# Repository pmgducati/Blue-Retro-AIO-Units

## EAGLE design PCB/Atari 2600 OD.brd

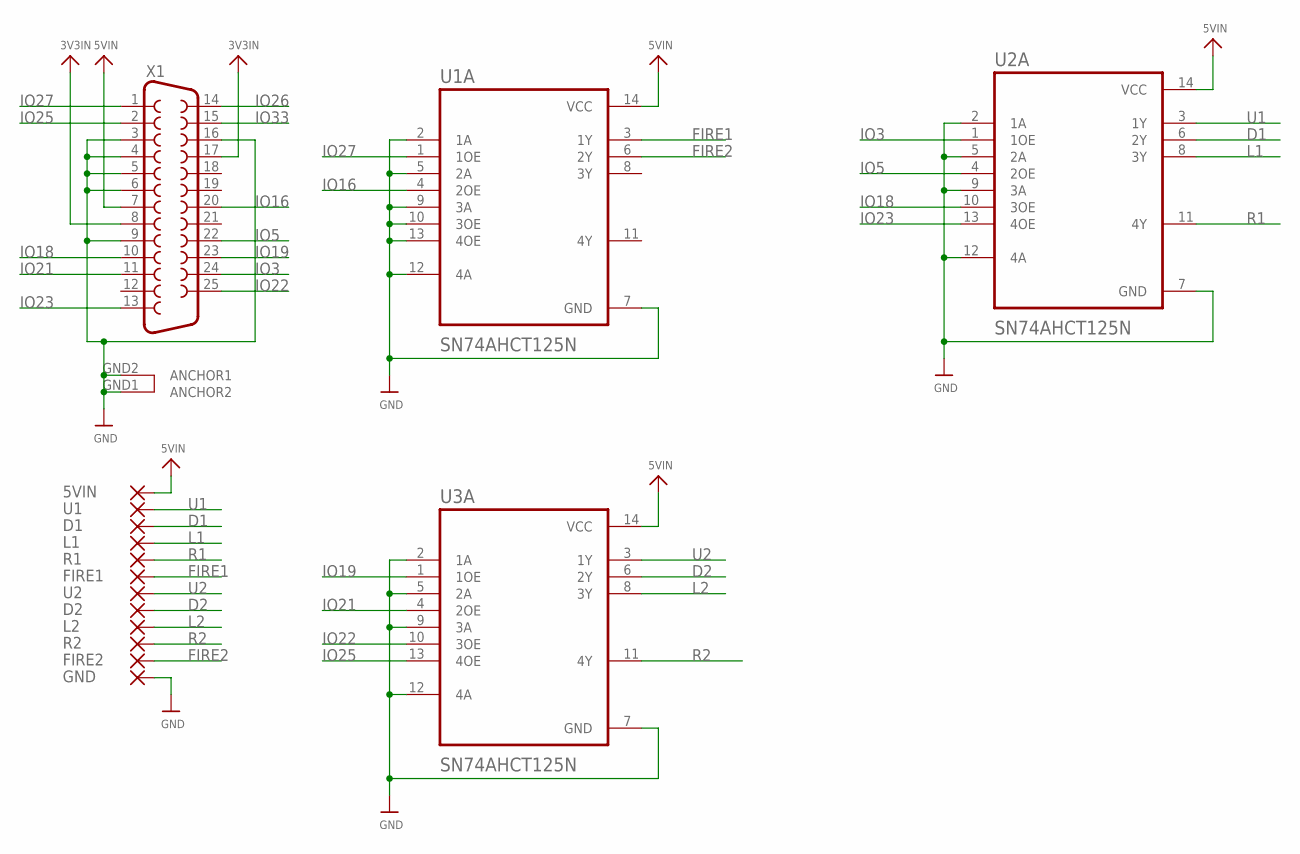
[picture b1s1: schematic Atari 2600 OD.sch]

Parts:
5VIN: SMD5; SMD2,54-5,08
D1, D2: SMD5; SMD2,54-5,08
FIRE1, FIRE2: SMD5; SMD2,54-5,08
GND: SMD5; SMD2,54-5,08
L1, L2: SMD5; SMD2,54-5,08
R1, R2: SMD5; SMD2,54-5,08
U1, U2: SMD5; SMD2,54-5,08
U1A, U2A, U3A: SN74AHCT125N; DIP794W45P254L1969H508Q14
X1: DB25_FEMALEHP; F25HP

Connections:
3V3IN: X1.8, X1.17
5VIN: 5VIN.1, U1A.14 (VCC), U2A.14 (VCC), U3A.14 (VCC), X1.7
D1: D1.1, U2A.6 (2Y)
D2: D2.1, U3A.6 (2Y)
FIRE1: FIRE1.1, U1A.3 (1Y)
FIRE2: FIRE2.1, U1A.6 (2Y)
GND: GND.1, U1A.2 (1A), U1A.5 (2A), U1A.7 (GND), U1A.9 (3A), U1A.10 (3OE), U1A.12 (4A), U1A.13 (4OE), U2A.2 (1A), U2A.5 (2A), U2A.7 (GND), U2A.9 (3A), U2A.12 (4A), U3A.2 (1A), U3A.5 (2A), U3A.7 (GND), U3A.9 (3A), U3A.12 (4A), X1.3, X1.4, X1.5, X1.6, X1.9, X1.16, X1.GND1 (ANCHOR2), X1.GND2 (ANCHOR1)
IO3: U2A.1 (1OE), X1.24
IO5: U2A.4 (2OE), X1.22
IO16: U1A.4 (2OE), X1.20
IO18: U2A.10 (3OE), X1.10
IO19: U3A.1 (1OE), X1.23
IO21: U3A.4 (2OE), X1.11
IO22: U3A.10 (3OE), X1.25
IO23: U2A.13 (4OE), X1.13
IO25: U3A.13 (4OE), X1.2
IO26: X1.14
IO27: U1A.1 (1OE), X1.1
IO33: X1.15
L1: L1.1, U2A.8 (3Y)
L2: L2.1, U3A.8 (3Y)
R1: R1.1, U2A.11 (4Y)
R2: R2.1, U3A.11 (4Y)
U1: U1.1, U2A.3 (1Y)
U2: U2.1, U3A.3 (1Y)

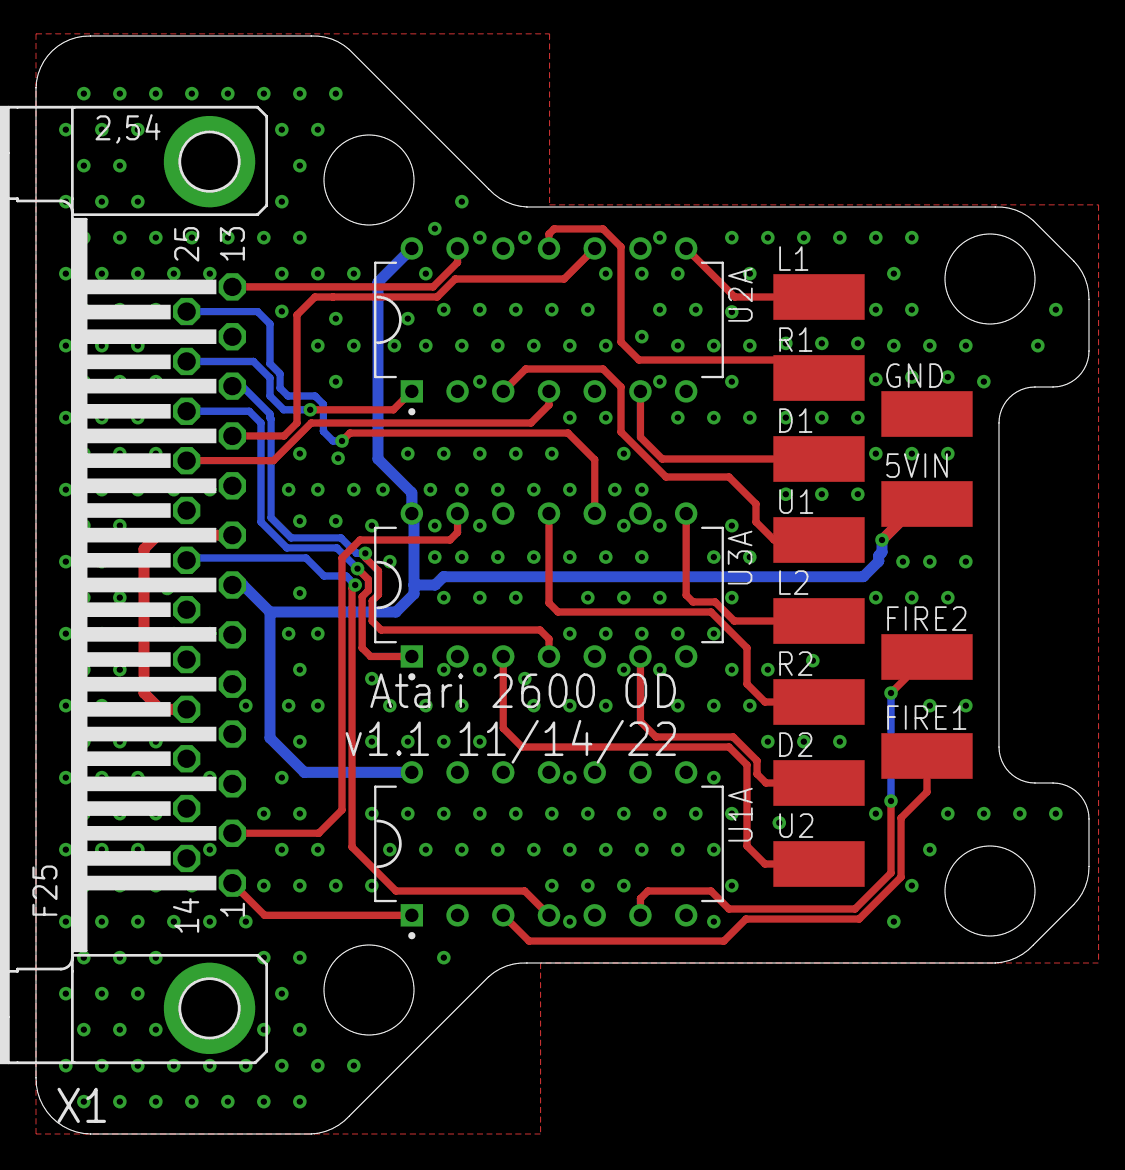
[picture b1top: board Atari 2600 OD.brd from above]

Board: 2 copper layers, 58.5 x 61.0 mm, 16 parts (0 on the bottom side), 23 nets.

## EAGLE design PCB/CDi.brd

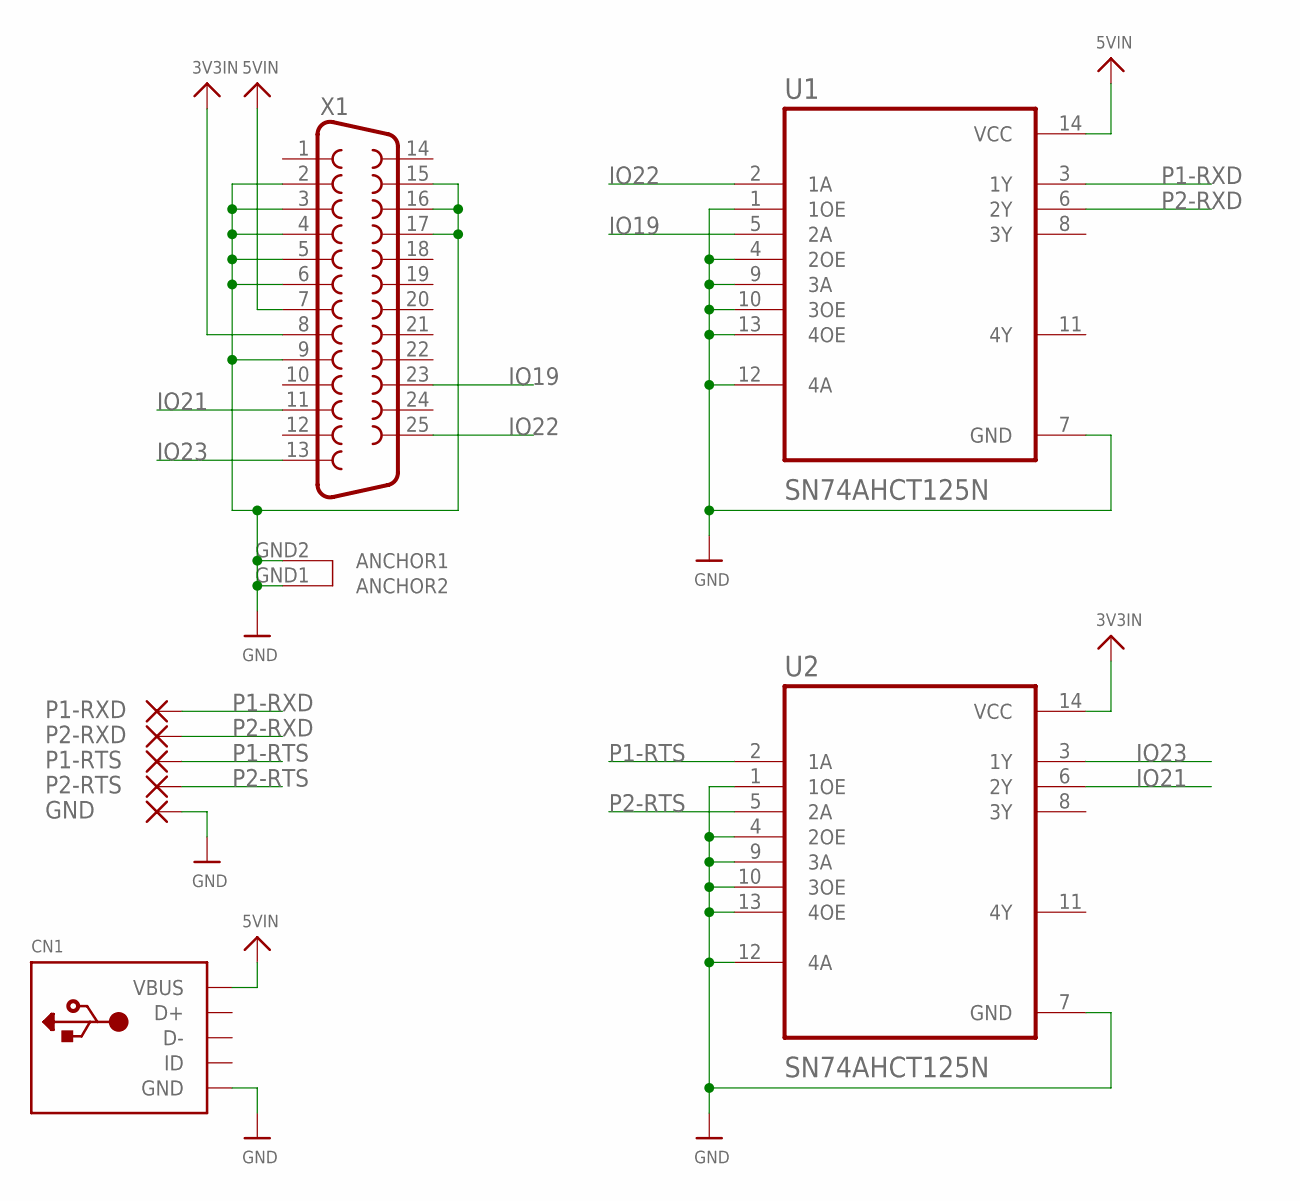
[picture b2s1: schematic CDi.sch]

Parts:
CN1: USBTHM; USB-MINIB-THM
GND: SMD5; SMD2,54-5,08
P1-RTS, P1-RXD, P2-RTS, P2-RXD: SMD5; SMD2,54-5,08
U1, U2: SN74AHCT125N; DIP794W45P254L1969H508Q14
X1: DB25_FEMALEHP; F25HP

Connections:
3V3IN: U2.14 (VCC), X1.8
5VIN: CN1.VBUS, U1.14 (VCC), X1.7
GND: CN1.GND, GND.1, U1.1 (1OE), U1.4 (2OE), U1.7 (GND), U1.9 (3A), U1.10 (3OE), U1.12 (4A), U1.13 (4OE), U2.1 (1OE), U2.4 (2OE), U2.7 (GND), U2.9 (3A), U2.10 (3OE), U2.12 (4A), U2.13 (4OE), X1.2, X1.3, X1.4, X1.5, X1.6, X1.9, X1.15, X1.16, X1.17, X1.GND1 (ANCHOR2), X1.GND2 (ANCHOR1)
IO19: U1.5 (2A), X1.23
IO21: U2.6 (2Y), X1.11
IO22: U1.2 (1A), X1.25
IO23: U2.3 (1Y), X1.13
P1-RTS: P1-RTS.1, U2.2 (1A)
P1-RXD: P1-RXD.1, U1.3 (1Y)
P2-RTS: P2-RTS.1, U2.5 (2A)
P2-RXD: P2-RXD.1, U1.6 (2Y)

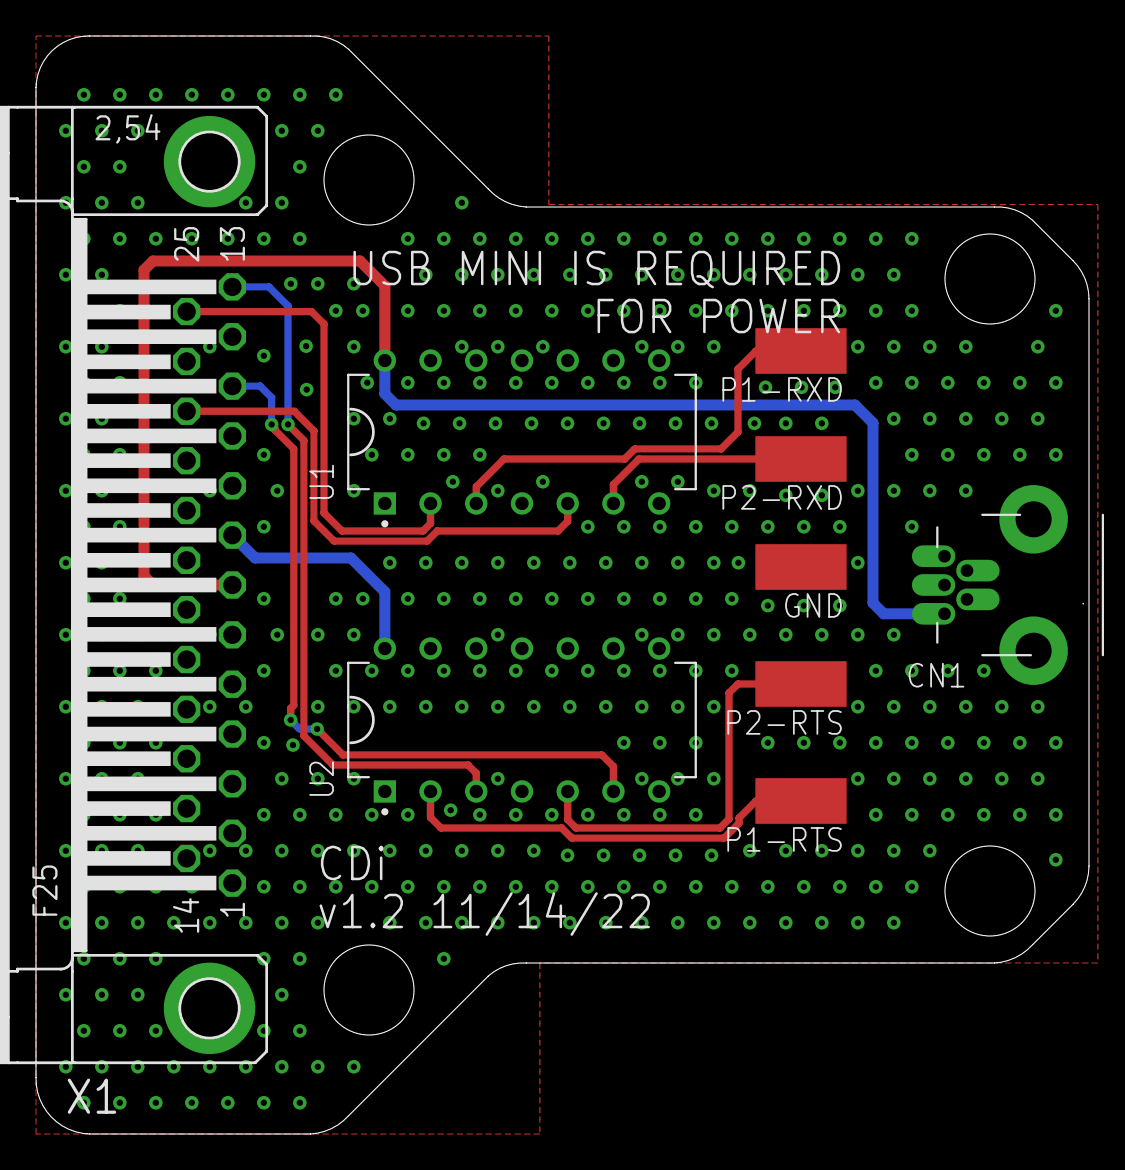
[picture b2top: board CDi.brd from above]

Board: 2 copper layers, 58.5 x 61.0 mm, 9 parts (0 on the bottom side), 11 nets.

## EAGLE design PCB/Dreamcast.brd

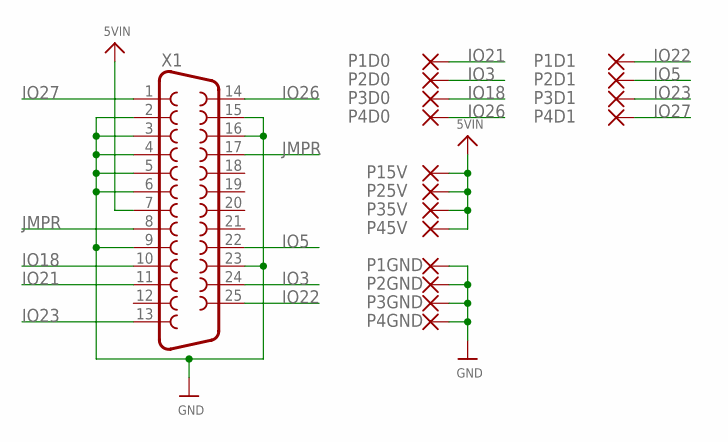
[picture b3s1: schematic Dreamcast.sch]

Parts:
P1D0, P1D1, P1GND, P2D0, P2D1, P2GND, P3D0, P3D1, P3GND, P4D0, P4D1, P4GND, P15V, P25V, P35V, P45V: SMD5; SMD2,54-5,08
X1: DB25_FEMALEH; F25H

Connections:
GND: P1GND.1, P2GND.1, P3GND.1, P4GND.1, X1.2, X1.3, X1.4, X1.5, X1.6, X1.9, X1.15, X1.16, X1.23, X1.GND1, X1.GND2
IO3: P2D0.1, X1.24
IO5: P2D1.1, X1.22
IO18: P3D0.1, X1.10
IO21: P1D0.1, X1.11
IO22: P1D1.1, X1.25
IO23: P3D1.1, X1.13
IO26: P4D0.1, X1.14
IO27: P4D1.1, X1.1
JMPR: X1.8, X1.17
VIN: P15V.1, P25V.1, P35V.1, P45V.1, X1.7

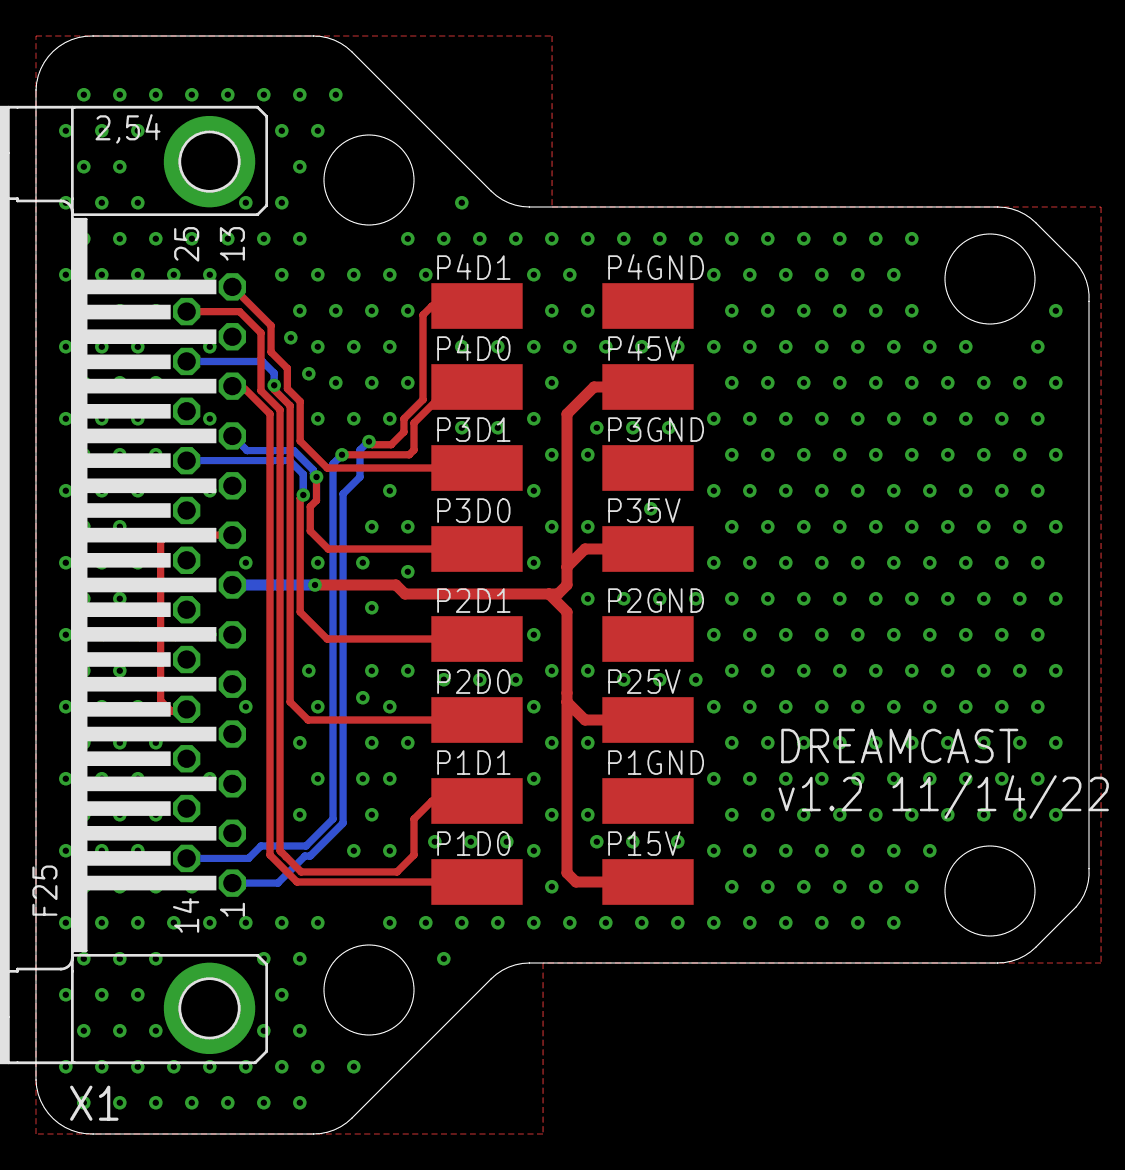
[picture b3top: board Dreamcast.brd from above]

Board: 2 copper layers, 58.5 x 61.0 mm, 17 parts (0 on the bottom side), 11 nets.

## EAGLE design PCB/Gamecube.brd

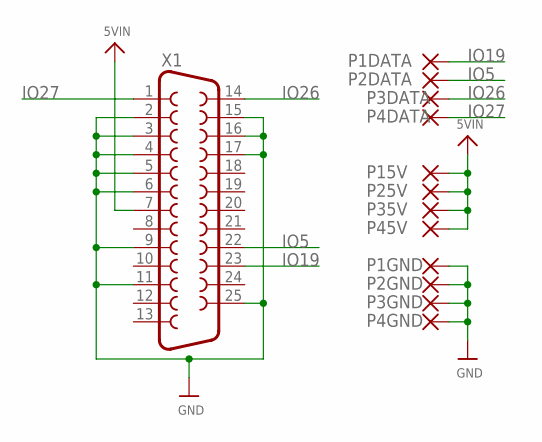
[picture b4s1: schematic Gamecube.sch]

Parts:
P1DATA, P1GND, P2DATA, P2GND, P3DATA, P3GND, P4DATA, P4GND, P15V, P25V, P35V, P45V: SMD5; SMD2,54-5,08
X1: DB25_FEMALEH; F25H

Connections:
5VIN: P15V.1, P25V.1, P35V.1, P45V.1, X1.7
GND: P1GND.1, P2GND.1, P3GND.1, P4GND.1, X1.2, X1.3, X1.4, X1.5, X1.6, X1.9, X1.11, X1.15, X1.16, X1.17, X1.25, X1.GND1, X1.GND2
IO5: P2DATA.1, X1.22
IO19: P1DATA.1, X1.23
IO26: P3DATA.1, X1.14
IO27: P4DATA.1, X1.1

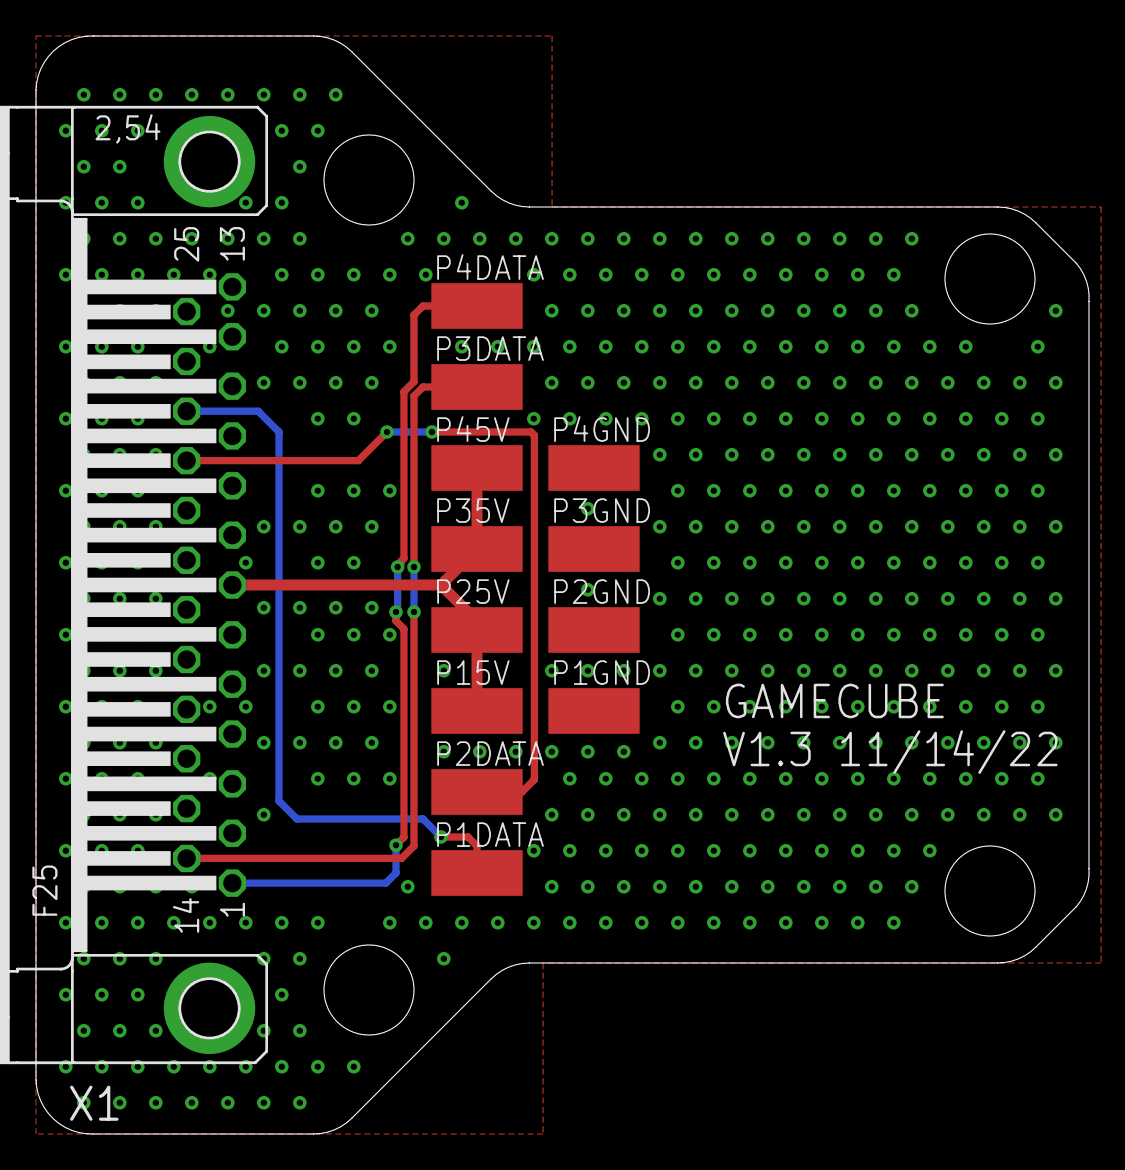
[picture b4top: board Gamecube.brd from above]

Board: 2 copper layers, 58.5 x 61.0 mm, 13 parts (0 on the bottom side), 6 nets.

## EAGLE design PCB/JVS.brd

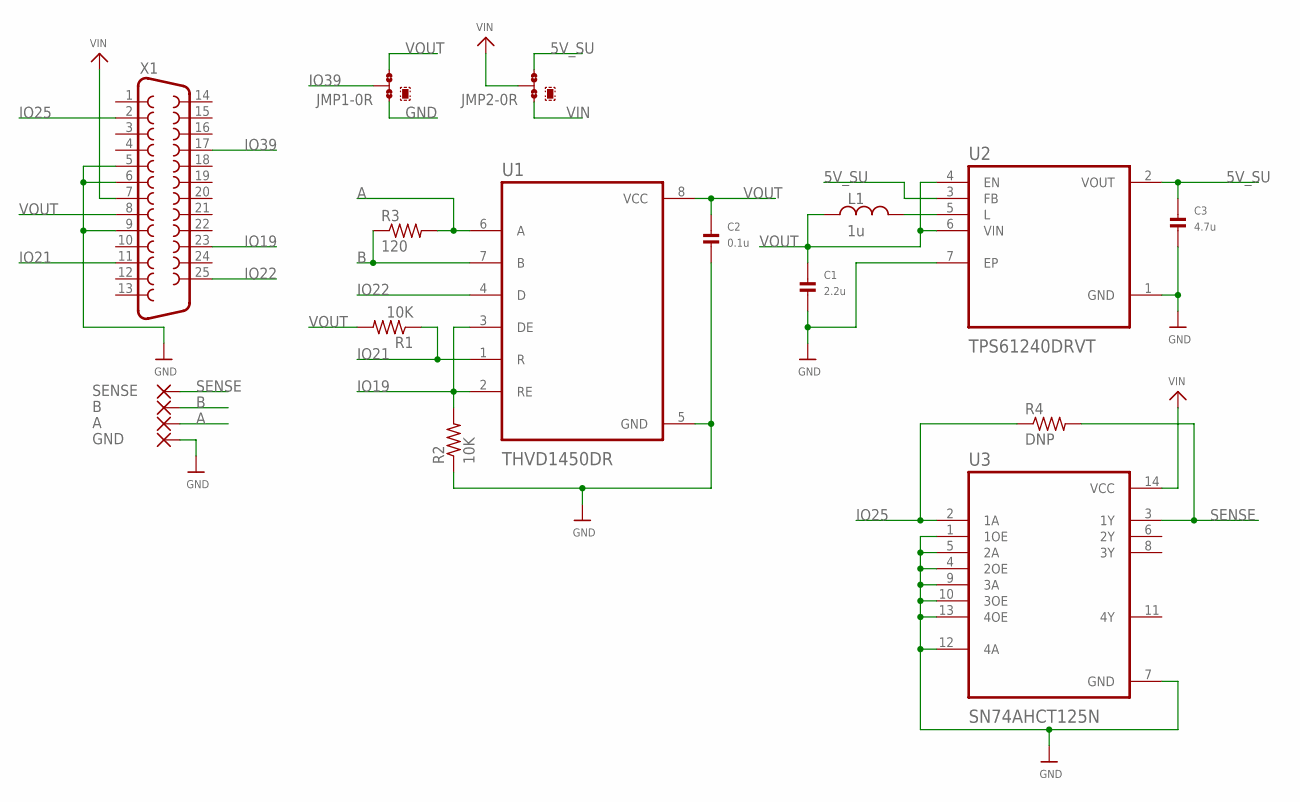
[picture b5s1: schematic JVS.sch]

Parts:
A: SMD5; SMD2,54-5,08
B: SMD5; SMD2,54-5,08
C1: 2.2u; 1206
C2: 0.1u; 1206
C3: 4.7u; 1206
GND: SMD5; SMD2,54-5,08
JMP1, JMP2: 0R-JUMPA; A0R-JMP
L1: 1u; INDC2009X120
R1, R2: 10K; R1206
R3: 120; R1206
R4: DNP; R1206
SENSE: SMD5; SMD2,54-5,08
U1: THVD1450DR; SOIC127P599X175-8N
U2: TPS61240DRVT; SON65P200X200X80-7N
U3: SN74AHCT125N; DIP794W45P254L1969H508Q14
X1: DB25_FEMALEH; F25H

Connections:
5V_SU: C3.1, JMP2.3, U2.2 (VOUT), U2.3 (FB)
A: A.1, R3.2, U1.6 (A)
B: B.1, R3.1, U1.7 (B)
GND: C1.2, C2.2, C3.2, GND.1, JMP1.1, R2.1, U1.5 (GND), U2.1 (GND), U2.7 (EP), U3.1 (1OE), U3.4 (2OE), U3.5 (2A), U3.7 (GND), U3.9 (3A), U3.10 (3OE), U3.12 (4A), U3.13 (4OE), X1.5, X1.6, X1.9
IO19: R2.2, U1.2 (RE), U1.3 (DE), X1.23
IO21: R1.1, U1.1 (R), X1.11
IO22: U1.4 (D), X1.25
IO25: R4.1, U3.2 (1A), X1.2
IO39: JMP1.2, X1.17
unnamed: L1.2, U2.5 (L)
SENSE: R4.2, SENSE.1, U3.3 (1Y)
VIN: JMP2.1, JMP2.2, U3.14 (VCC), X1.7
VOUT: C1.1, C2.1, JMP1.3, L1.1, R1.2, U1.8 (VCC), U2.4 (EN), U2.6 (VIN), X1.8

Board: 2 copper layers, 18 parts (0 on the bottom side), 13 nets, no tracks yet.

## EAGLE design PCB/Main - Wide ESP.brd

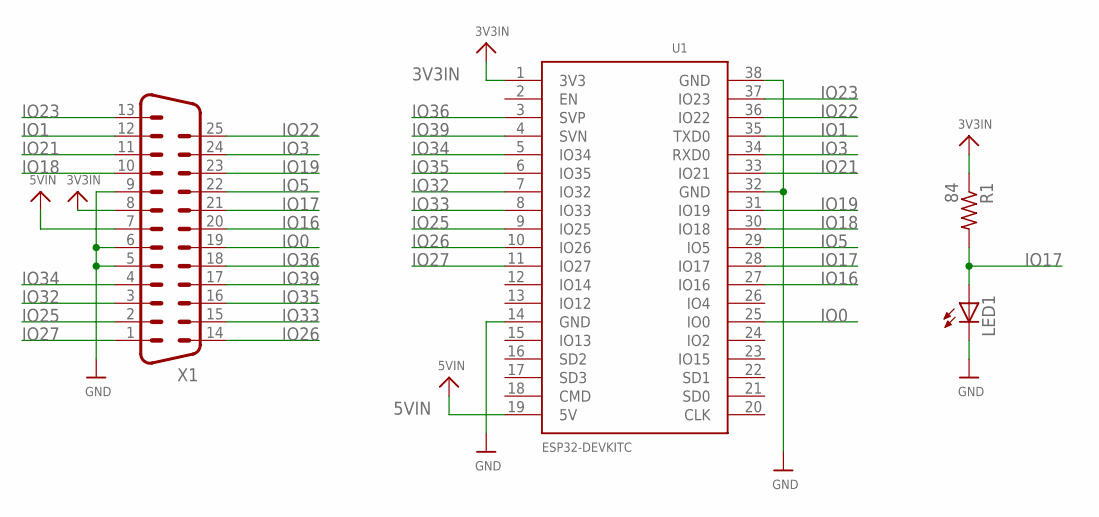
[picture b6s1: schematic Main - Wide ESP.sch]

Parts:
LED1: LEDCHIPLED_1206; CHIPLED_1206
R1: 84; R1206
U1: ESP32DEVKITC; ESP32-DEVKITC
X1: DB25_MALEH; M25H

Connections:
3V3IN: R1.1, U1.1 (3V3), X1.8
5VIN: U1.19 (5V), X1.7
GND: LED1.C, U1.14 (GND), U1.32 (GND), U1.38 (GND), X1.5, X1.6, X1.9
IO0: U1.25 (IO0), X1.19
IO1: U1.35 (TXD0), X1.12
IO3: U1.34 (RXD0), X1.24
IO5: U1.29 (IO5), X1.22
IO16: U1.27 (IO16), X1.20
IO17: LED1.A, R1.2, U1.28 (IO17), X1.21
IO18: U1.30 (IO18), X1.10
IO19: U1.31 (IO19), X1.23
IO21: U1.33 (IO21), X1.11
IO22: U1.36 (IO22), X1.25
IO23: U1.37 (IO23), X1.13
IO25: U1.9 (IO25), X1.2
IO26: U1.10 (IO26), X1.14
IO27: U1.11 (IO27), X1.1
IO32: U1.7 (IO32), X1.3
IO33: U1.8 (IO33), X1.15
IO34: U1.5 (IO34), X1.4
IO35: U1.6 (IO35), X1.16
IO36: U1.3 (SVP), X1.18
IO39: U1.4 (SVN), X1.17

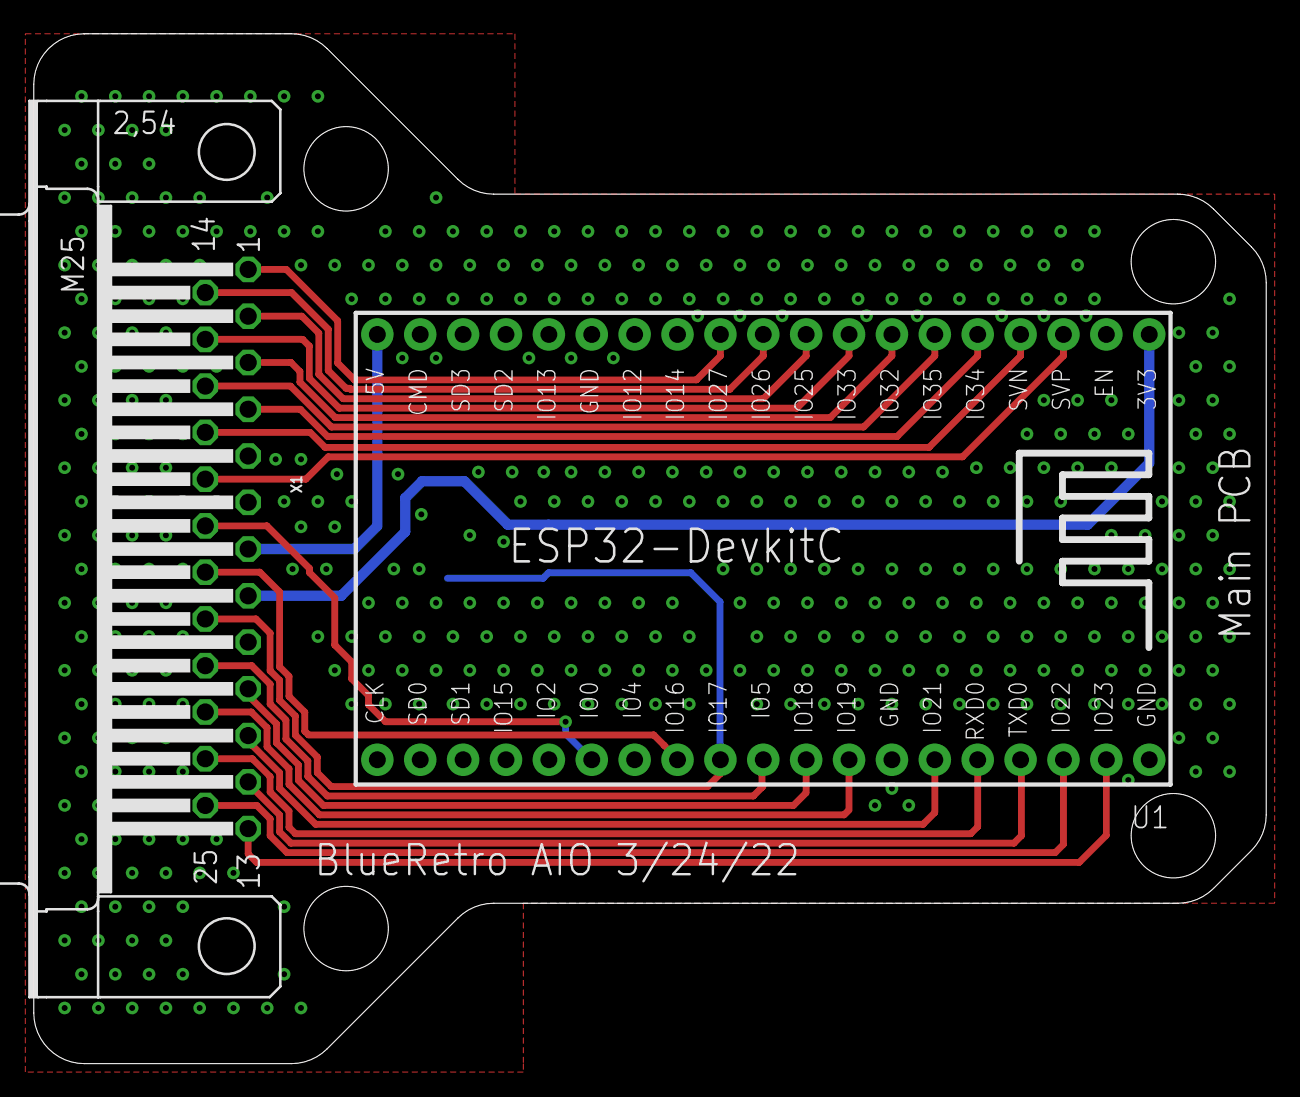
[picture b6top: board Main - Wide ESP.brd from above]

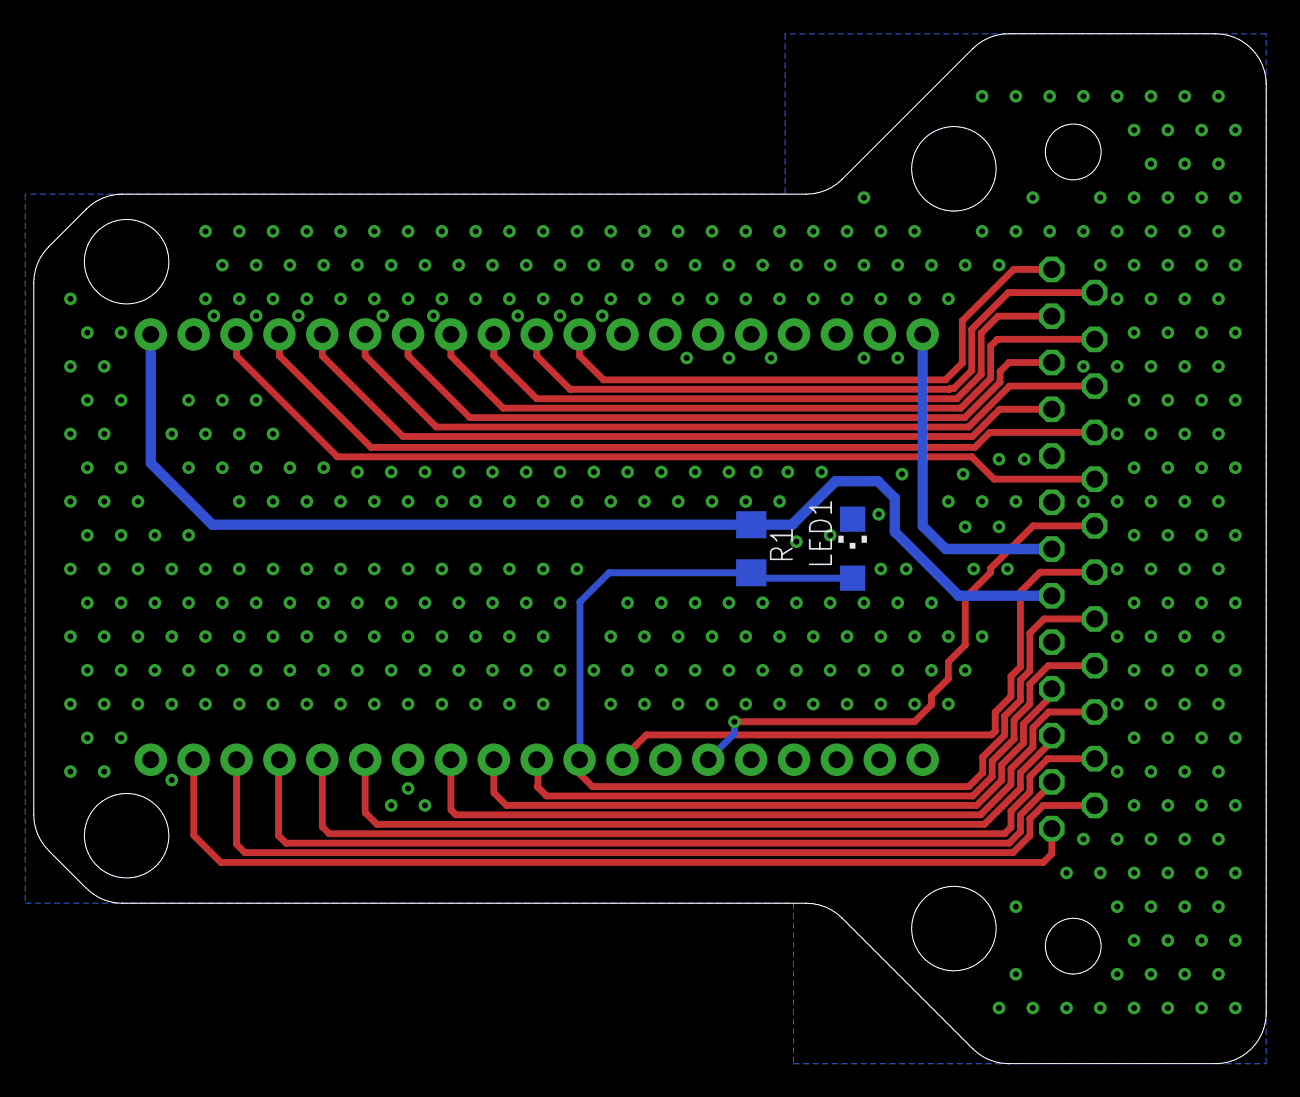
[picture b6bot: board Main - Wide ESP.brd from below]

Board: 2 copper layers, 73.0 x 61.0 mm, 4 parts (2 on the bottom side), 23 nets.

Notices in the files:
parts and their libraries:
SparkFun-Retired: Licensing: Creative Commons ShareAlike 4.0 International - https://creativecommons.org/licenses/by-sa/4.0
microbuilder: This work is placed in the public domain, and may be freely used for commercial and non-commercial work with the following conditions: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
